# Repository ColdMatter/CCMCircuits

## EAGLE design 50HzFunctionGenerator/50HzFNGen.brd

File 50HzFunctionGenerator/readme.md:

50Hz Triangular wave generator

This circuit takes a 50Hz square wave and integrates it to turn  it into a triangular wave. 
The gain of the integrator is controlled via a trimpot and rotary switch. An external voltage offset
can also be added. This circuit is designed to drive the thorlabs cavities used in the transfer cavity
lock

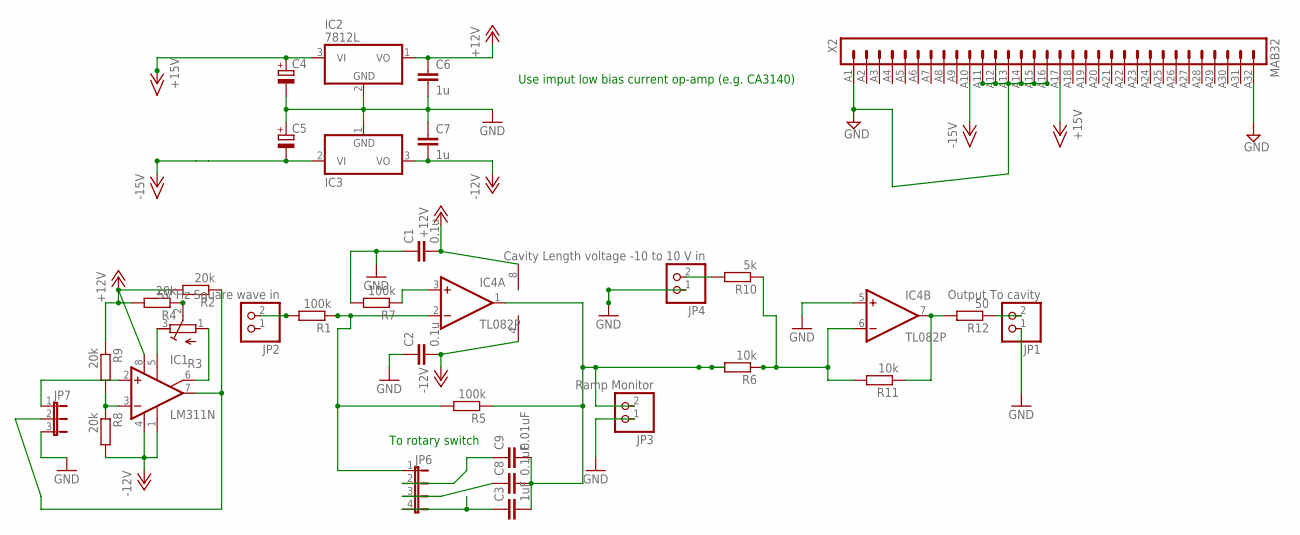
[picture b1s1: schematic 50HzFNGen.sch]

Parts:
C1, C2: 0.1u; C025-025X050
C3: 1uF; C225-062X268
C4, C5: CPOL-EUE5-8.5; E5-8,5
C6, C7: 1u; C050-030X075
C8: 0.1uF; C102-043X133
C9: 0.01uF; C050-025X075
IC1: LM311N; DIL08
IC2: 7812L; TO92
IC3: 7912L; TO92
IC4: TL082P; DIL08
JP1: Output To cavity; 1X02
JP2: 5V Hz Square wave in; 1X02
JP3: Ramp Monitor; 1X02
JP4: Cavity Length voltage -10 to 10 V in; 1X02
JP6: JP4E; JP4
JP7: JP2E; JP2
R1, R5, R7: 100k; 0207/10
R2, R4, R8, R9: 20k; 0207/10
R3: R-TRIMM64P; RTRIM64P
R6, R11: 10k; 0207/10
R10: 5k; 0207/10
R12: 50; 0207/10
X2: MAB32

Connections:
+12V: C1.2, C6.1, IC1.8 (V+), IC2.1 (VO), IC4.8 (V+), R2.2, R4.2, R9.1
+15V: C4.+, IC2.3 (VI), X2.A17 (17)
-12V: C2.2, C7.2, IC1.1 (GND), IC1.4 (V-), IC3.3 (VO), IC4.4 (V-), R8.2
-15V: C5.-, IC3.2 (VI), X2.A10 (10)
GND: C1.1, C2.1, C4.-, C5.+, C6.2, C7.1, IC2.2 (GND), IC3.1 (GND), IC4.5 (+IN), JP1.1, JP3.1, JP4.1, JP7.3, R7.2, X2.A1 (1), X2.A11 (11), X2.A12 (12), X2.A14 (14), X2.A15 (15), X2.A16 (16), X2.A32 (32)
unnamed: C3.1, JP6.4
unnamed: IC4.6 (-IN), R6.1, R10.1, R11.2
unnamed: IC4.7 (OUT), R11.1, R12.2
unnamed: JP1.2, R12.1
unnamed: C8.1, JP6.3
unnamed: IC1.7 (OUT), JP7.2, R2.1
unnamed: JP2.2, R1.2
unnamed: C3.2, C8.2, C9.2, IC4.1 (OUT), JP3.2, R5.1, R6.2
unnamed: C9.1, JP6.2
unnamed: IC1.5 (ON), R3.3 (A)
unnamed: IC4.2 (-IN), JP6.1, R1.1, R5.2
unnamed: IC1.6 (ON/STR), R3.1 (E)
unnamed: R3.2 (S), R4.1
unnamed: IC4.3 (+IN), R7.1
unnamed: JP4.2, R10.2
unnamed: IC1.2 (+IN), JP7.1
unnamed: IC1.3 (-IN), R8.1, R9.2

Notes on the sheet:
Use imput low bias current op-amp (e.g. CA3140)
To rotary switch

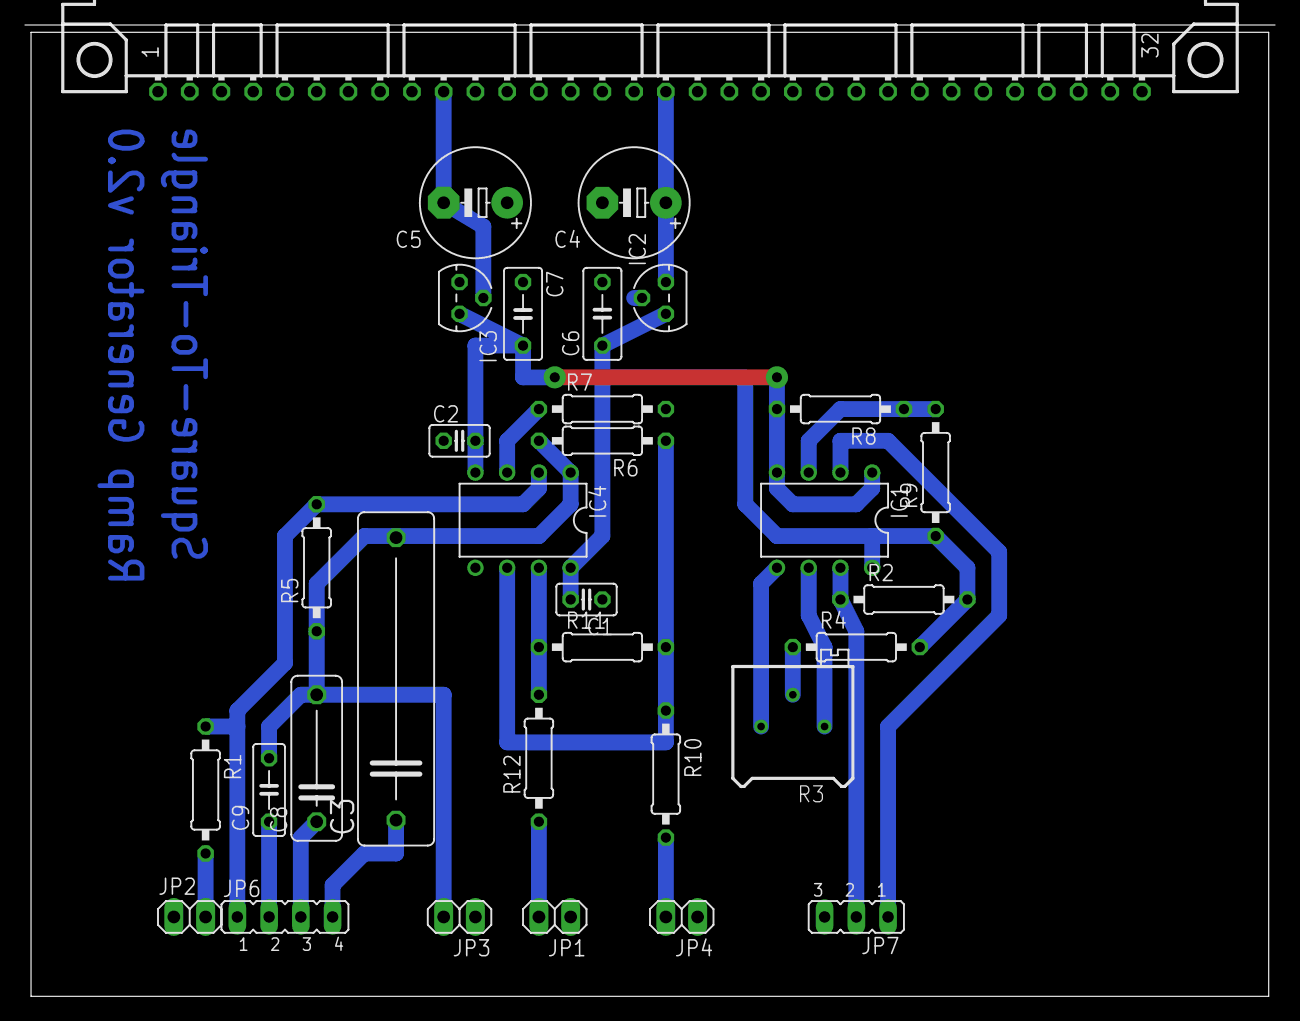
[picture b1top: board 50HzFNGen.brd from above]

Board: 2 copper layers, 100.0 x 77.7 mm, 32 parts (0 on the bottom side), 22 nets.

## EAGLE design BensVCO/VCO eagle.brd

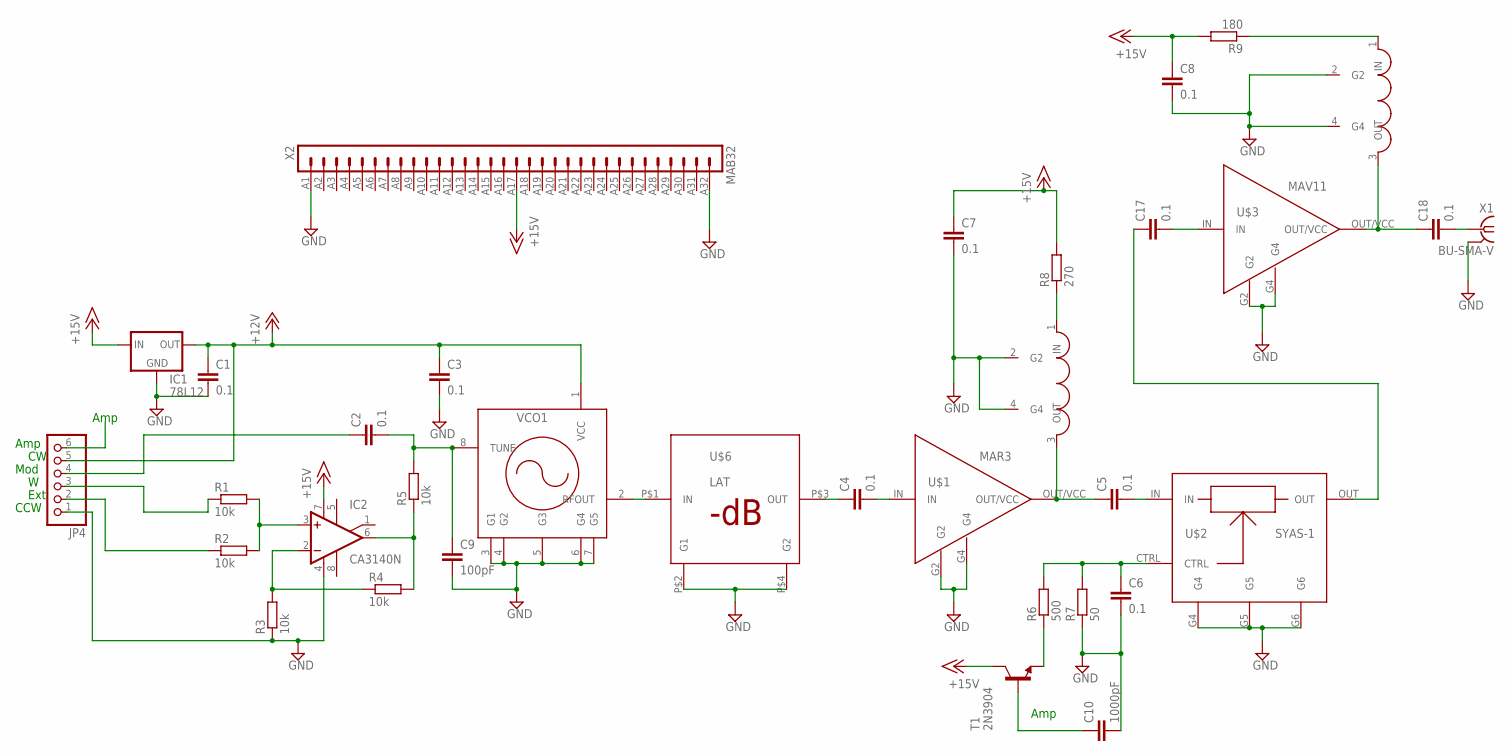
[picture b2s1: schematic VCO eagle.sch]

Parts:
C1, C2, C3, C4, C5, C6, C7, C8: 0.1; C1210
C9: 100pF; C0805
C10: 1000pF; C0805
C17, C18: 0.1; C1206
IC1: 78L12; 78LXX
IC2: CA3140N; DIL08
JP4: PINHD-1X6; 1X06
R1, R2, R3, R4, R5: 10k; 0204/7
R6: 500; 0204/7
R7: 50; 0204/7
R8: 270; R1206
R9: 180; R1206
T1: 2N3904; TO92
U$1: MAR3; MAR
U$2: SYAS-1; TTT166
U$3: MAV11; MAR
U$4, U$5: TCCH-80; PL-147
U$6: LAT; MMM168
VCO1: POS; A01
X1: BU-SMA-V
X2: MAB32

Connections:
+12V: C1.1, C3.1, IC1.OUT, JP4.5, VCO1.1 (VCC)
+15V: C7.1, C8.1, IC1.IN, IC2.7 (V+), R8.2, R9.2, T1.1 (C), X2.A17 (17)
AMP: C10.1, JP4.6, T1.2 (B)
GND: C1.2, C3.2, C6.2, C7.2, C8.2, C9.2, C10.2, IC1.GND, IC2.4 (V-), JP4.1, R3.1, R7.1, U$1.G2, U$1.G4, U$2.G4, U$2.G5, U$2.G6, U$3.G2, U$3.G4, U$4.2 (G2), U$4.4 (G4), U$5.2 (G2), U$5.4 (G4), U$6.P$2 (G1), U$6.P$4 (G2), VCO1.3 (G1), VCO1.4 (G2), VCO1.5 (G3), VCO1.6 (G4), VCO1.7 (G5), X1.2 (GND), X1.3 (GND), X1.4 (GND), X1.5 (GND), X2.A1 (1), X2.A32 (32)
unnamed: R6.1, T1.3 (E)
unnamed: JP4.2, R2.1
unnamed: IC2.3 (+IN), R1.2, R2.2
unnamed: IC2.2 (-IN), R3.2, R4.1
unnamed: IC2.6 (OUT), R4.2, R5.1
unnamed: C6.1, R6.2, R7.2, U$2.CTRL
unnamed: C2.1, JP4.4
unnamed: C2.2, C9.1, R5.2, VCO1.8 (TUNE)
unnamed: R9.1, U$5.1 (IN)
unnamed: U$6.P$1 (IN), VCO1.2 (RFOUT)
unnamed: C4.1, U$6.P$3 (OUT)
unnamed: C4.2, U$1.IN
unnamed: C5.1, U$1.OUT/VCC, U$4.3 (OUT)
unnamed: C5.2, U$2.IN
unnamed: C17.2, U$3.IN
unnamed: C18.1, U$3.OUT/VCC, U$5.3 (OUT)
unnamed: R8.1, U$4.1 (IN)
unnamed: C17.1, U$2.OUT
unnamed: C18.2, X1.1
unnamed: JP4.3, R1.1

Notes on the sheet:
CCW
Mod
Ext
Amp

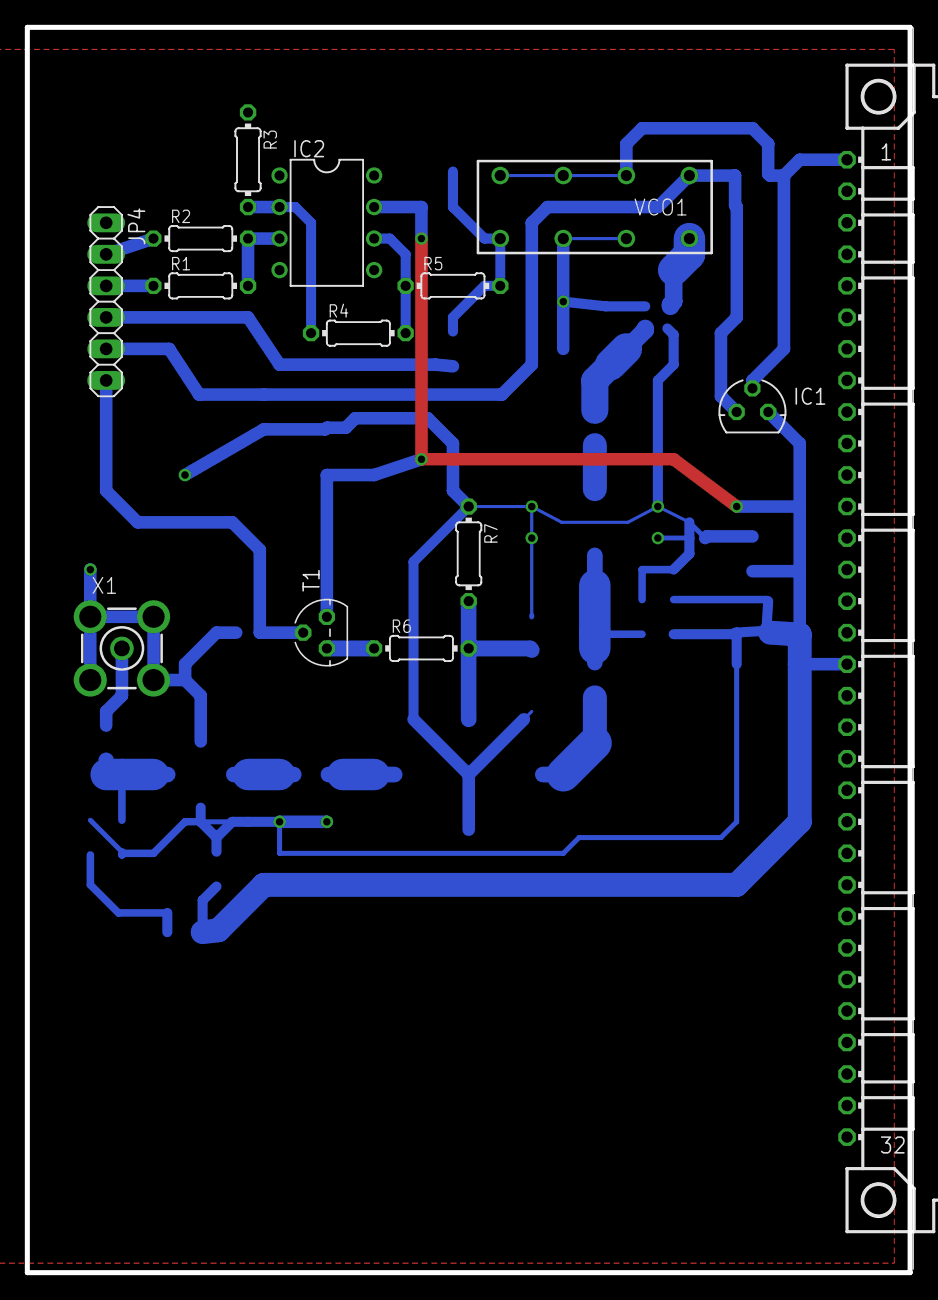
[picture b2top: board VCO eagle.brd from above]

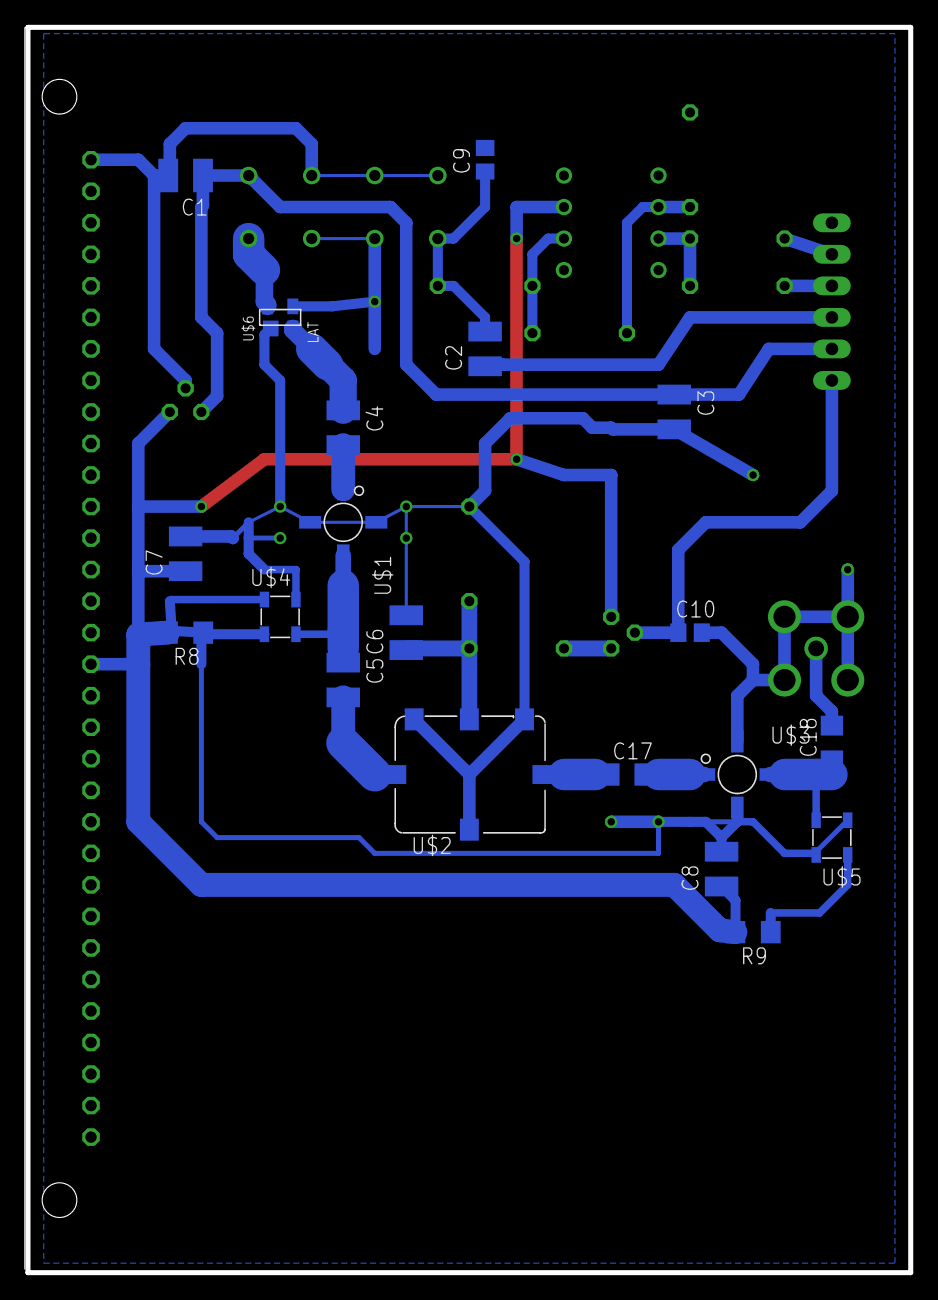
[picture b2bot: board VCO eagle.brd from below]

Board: 2 copper layers, 71.1 x 100.3 mm, 34 parts (20 on the bottom side), 24 nets.

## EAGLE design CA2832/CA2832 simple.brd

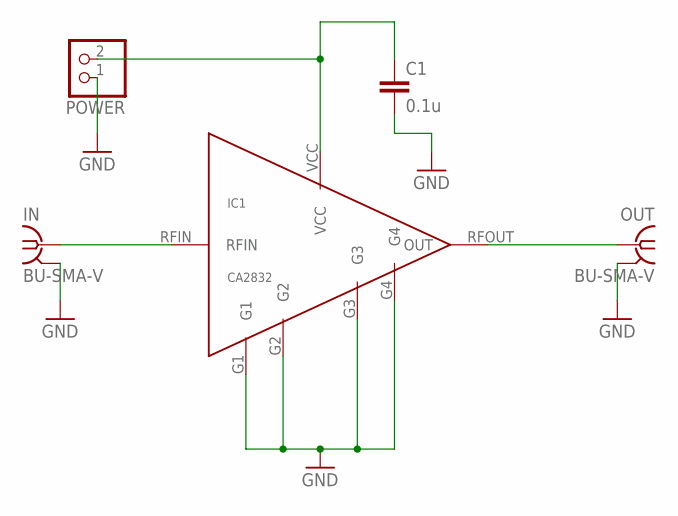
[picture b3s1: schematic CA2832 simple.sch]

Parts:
C1: 0.1u; C1206
IC1: CA2832; 714F-03
IN: BU-SMA-V
OUT: BU-SMA-V
POWER: PINHD-1X2; 1X02

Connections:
GND: C1.2, IC1.G1, IC1.G2, IC1.G3, IC1.G4, IN.2, IN.3 (2), IN.4 (2), IN.5 (2), OUT.2, OUT.3 (2), OUT.4 (2), OUT.5 (2), POWER.1
unnamed: IC1.RFIN, IN.1
unnamed: IC1.RFOUT (OUT), OUT.1
VCC: C1.1, IC1.VCC, POWER.2

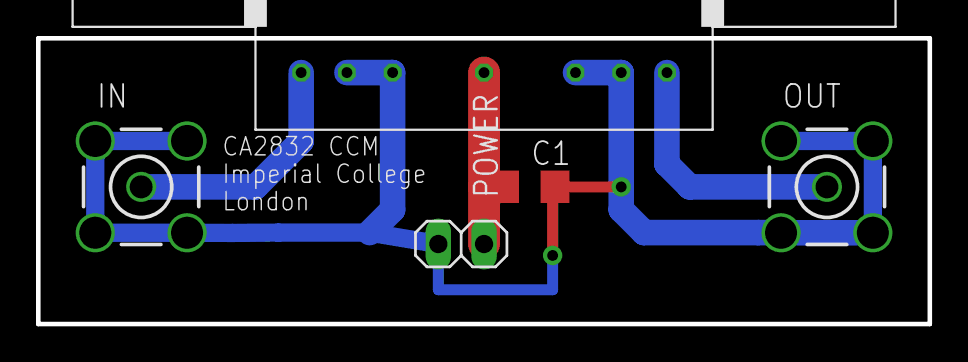
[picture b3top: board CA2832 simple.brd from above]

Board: 2 copper layers, 49.5 x 15.9 mm, 5 parts (0 on the bottom side), 4 nets.

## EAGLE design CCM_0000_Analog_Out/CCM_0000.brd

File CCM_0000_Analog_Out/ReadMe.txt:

This is a simple analog output board useful for providing an adjustable voltage to a pzt amplifier, cavity, etc.  Jumpers allow the user to choose between unipolar and bipolar operation.  Substituting various LM-4040 (or equivalent) reference diodes allows the voltage ranges to be adjusted.  

Currently, everyone in the lab uses 9V batteries with old-school trimpots wired up to them for this type of application.  Unsurprisingly, nobody ever remembers to disconnect the battery when they are finished.  As a result, we have lots of dead 9V batteries in the lab.  I've remedied the problem temporarily with some rechargeable batteries, but the practice is still stupid.

It might be a better idea to do a multi-channel board that fits nicely in a NIM rack...

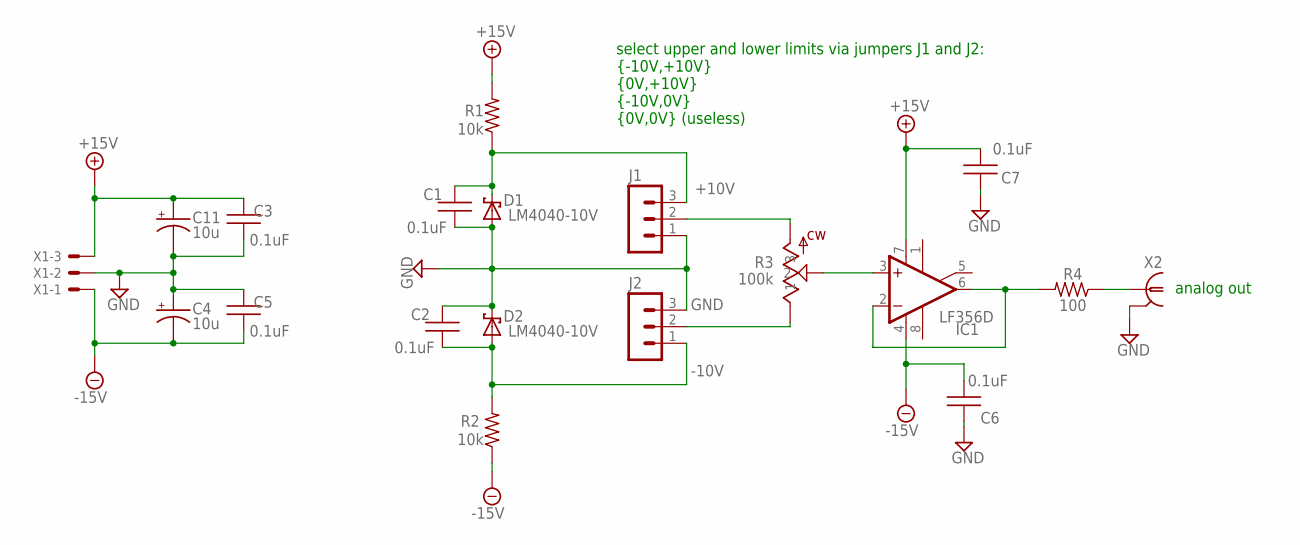
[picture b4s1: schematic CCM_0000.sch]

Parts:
C1, C2, C3, C5, C6, C7: 0.1uF; 0603
C4, C11: 10u; EIA3216
D1, D2: LM4040-10V; SOT23
IC1: LF356D; SO08
J1, J2: MA03-1
R1, R2: 10k; 0603
R3: 100k; 3590
R4: 100; 0603
X1: 22-23-2031
X2: 1-227161-0; AMP_227161

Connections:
+10V: C1.1, D1.1 (C), J1.3, R1.1
+15V: C3.1, C7.2, C11.A (+), IC1.7 (V+), R1.2, X1.3
-10V: C2.2, D2.2 (A), J2.1, R2.2
-15V: C4.C (-), C5.2, C6.2, IC1.4 (V-), R2.1, X1.1
GND: C1.2, C2.1, C3.2, C4.A (+), C5.1, C6.1, C7.1, C11.C (-), D1.2 (A), D2.1 (C), J1.1, J2.3, X1.2, X2.2
unnamed: J1.2, R3.3
unnamed: J2.2, R3.1
unnamed: R4.1, X2.1
unnamed: IC1.2 (-IN), IC1.6 (OUT), R4.2
unnamed: IC1.3 (+IN), R3.2

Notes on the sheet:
select upper and lower limits via jumpers J1 and J2: {-10V,+10V} {0V,+10V} {-10V,0V} {0V,0V} (useless)
analog out

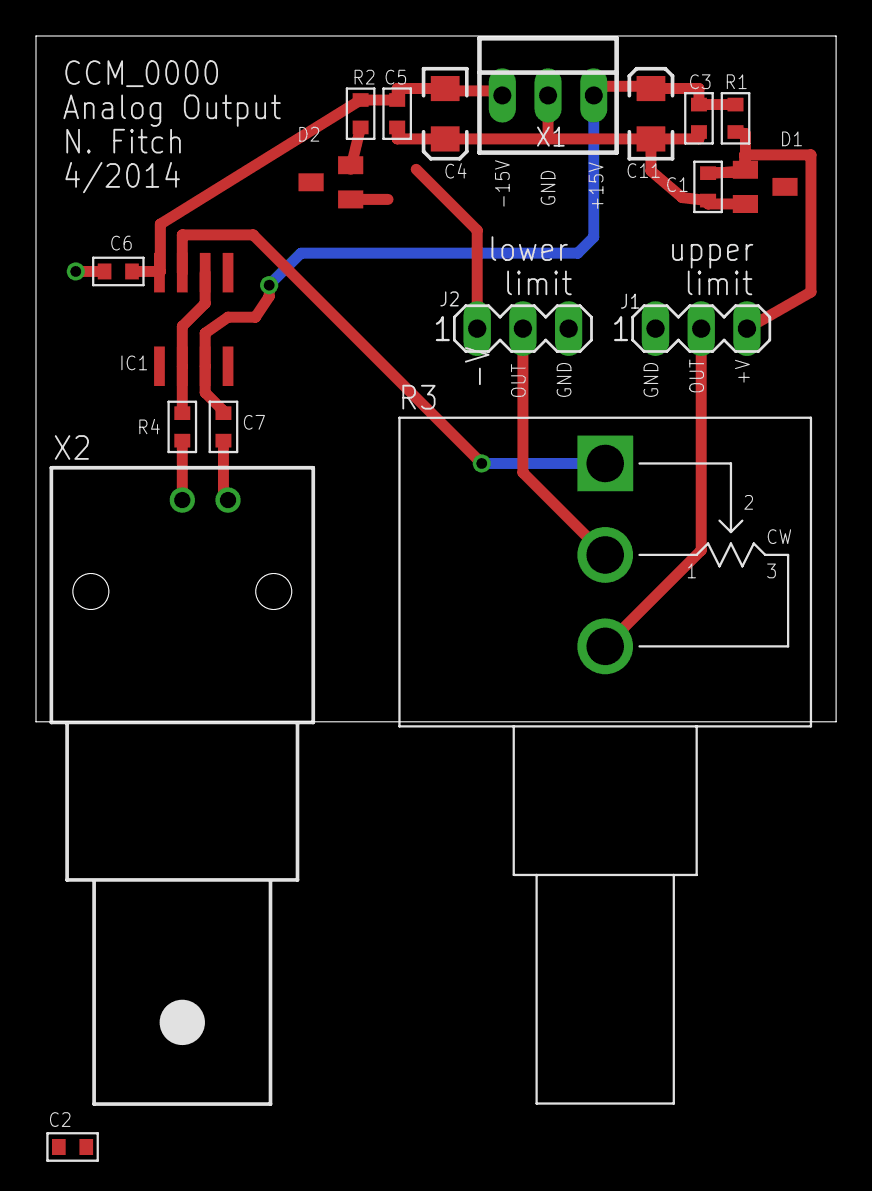
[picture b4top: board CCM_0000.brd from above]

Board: 2 copper layers, 44.5 x 38.1 mm, 19 parts (0 on the bottom side), 10 nets.

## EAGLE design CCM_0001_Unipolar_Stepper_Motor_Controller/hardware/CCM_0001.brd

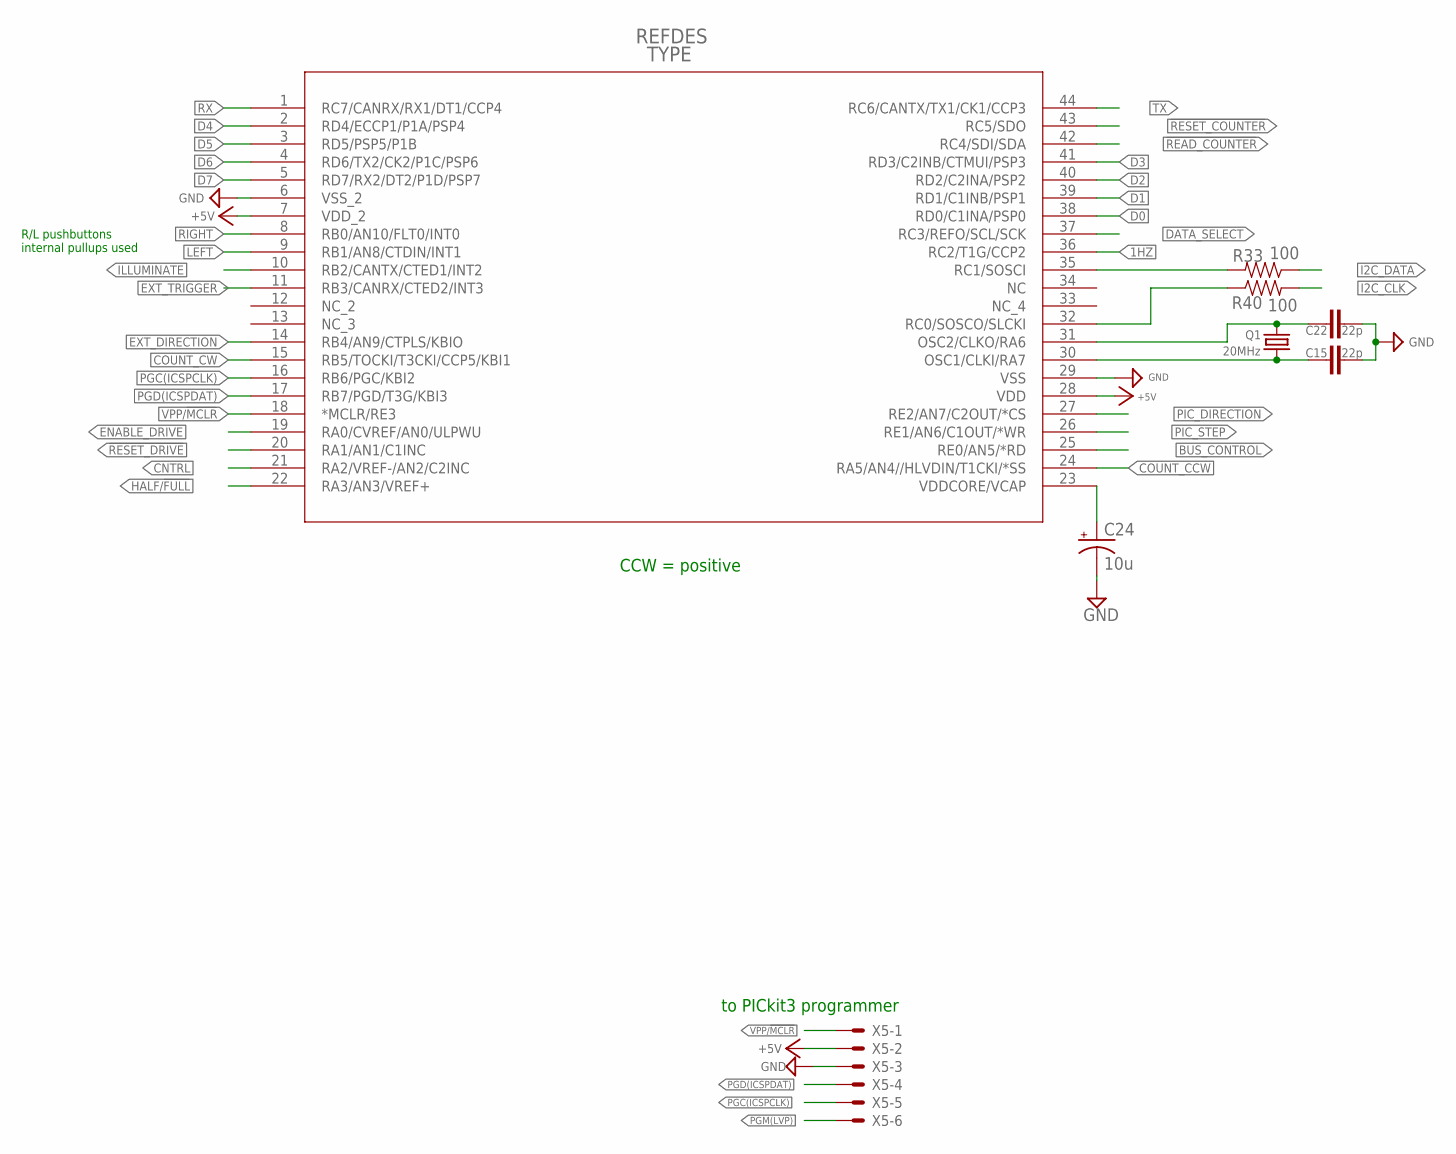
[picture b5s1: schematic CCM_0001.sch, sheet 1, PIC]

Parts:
C15, C22: 22p; 0603-CAP
C24: 10u; EIA3216
IC18: PIC18F46K80; TQFP44_MC
Q1: 20MHz; TC26V
R33, R40: 100; 0603-RES
X5: 22-23-2061

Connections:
1HZ: IC18.36 (RC2/T1G/CCP2); also elsewhere on the board
!READ_COUNTER: IC18.42 (RC4/SDI/SDA); also elsewhere on the board
!RESET_COUNTER: IC18.43 (RC5/SDO); also elsewhere on the board
!RESET_DRIVE: IC18.20 (RA1/AN1/C1INC); also elsewhere on the board
+5V: IC18.7 (VDD_2), IC18.28 (VDD), X5.2; also elsewhere on the board
BUS_CONTROL: IC18.25 (RE0/AN5/*RD); also elsewhere on the board
CNTRL: IC18.21 (RA2/VREF-/AN2/C2INC); also elsewhere on the board
COUNT_CCW: IC18.24 (RA5/AN4//HLVDIN/T1CKI/*SS); also elsewhere on the board
COUNT_CW: IC18.15 (RB5/TOCKI/T3CKI/CCP5/KBI1); also elsewhere on the board
D0: IC18.38 (RD0/C1INA/PSP0); also elsewhere on the board
D1: IC18.39 (RD1/C1INB/PSP1); also elsewhere on the board
D2: IC18.40 (RD2/C2INA/PSP2); also elsewhere on the board
D3: IC18.41 (RD3/C2INB/CTMUI/PSP3); also elsewhere on the board
D4: IC18.2 (RD4/ECCP1/P1A/PSP4); also elsewhere on the board
D5: IC18.3 (RD5/PSP5/P1B); also elsewhere on the board
D6: IC18.4 (RD6/TX2/CK2/P1C/PSP6); also elsewhere on the board
D7: IC18.5 (RD7/RX2/DT2/P1D/PSP7); also elsewhere on the board
DATA_SELECT: IC18.37 (RC3/REFO/SCL/SCK); also elsewhere on the board
ENABLE_DRIVE: IC18.19 (RA0/CVREF/AN0/ULPWU); also elsewhere on the board
EXT_DIRECTION: IC18.14 (RB4/AN9/CTPLS/KBIO); also elsewhere on the board
EXT_TRIGGER: IC18.11 (RB3/CANRX/CTED2/INT3); also elsewhere on the board
GND: C15.1, C22.1, C24.C (-), IC18.6 (VSS_2), IC18.29 (VSS), X5.3; also elsewhere on the board
HALF/!FULL: IC18.22 (RA3/AN3/VREF+); also elsewhere on the board
I2C_CLK: R40.2; also elsewhere on the board
I2C_DATA: R33.1; also elsewhere on the board
ILLUMINATE: IC18.10 (RB2/CANTX/CTED1/INT2); also elsewhere on the board
LEFT: IC18.9 (RB1/AN8/CTDIN/INT1); also elsewhere on the board
unnamed: C15.2, IC18.30 (OSC1/CLKI/RA7), Q1.1
unnamed: C22.2, IC18.31 (OSC2/CLKO/RA6), Q1.2
unnamed: C24.A (+), IC18.23 (VDDCORE/VCAP)
unnamed: IC18.35 (RC1/SOSCI), R33.2
unnamed: IC18.32 (RC0/SOSCO/SLCKI), R40.1
PGC(ICSPCLK): IC18.16 (RB6/PGC/KBI2), X5.5
PGD(ICSPDAT): IC18.17 (RB7/PGD/T3G/KBI3), X5.4
PGM(LVP): X5.6
PIC_DIRECTION: IC18.27 (RE2/AN7/C2OUT/*CS); also elsewhere on the board
PIC_STEP: IC18.26 (RE1/AN6/C1OUT/*WR); also elsewhere on the board
RIGHT: IC18.8 (RB0/AN10/FLT0/INT0); also elsewhere on the board
RX: IC18.1 (RC7/CANRX/RX1/DT1/CCP4); also elsewhere on the board
TX: IC18.44 (RC6/CANTX/TX1/CK1/CCP3); also elsewhere on the board
VPP/!MCLR: IC18.18 (*MCLR/RE3), X5.1

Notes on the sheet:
to PICkit3 programmer
R/L pushbuttons internal pullups used
CCW = positive

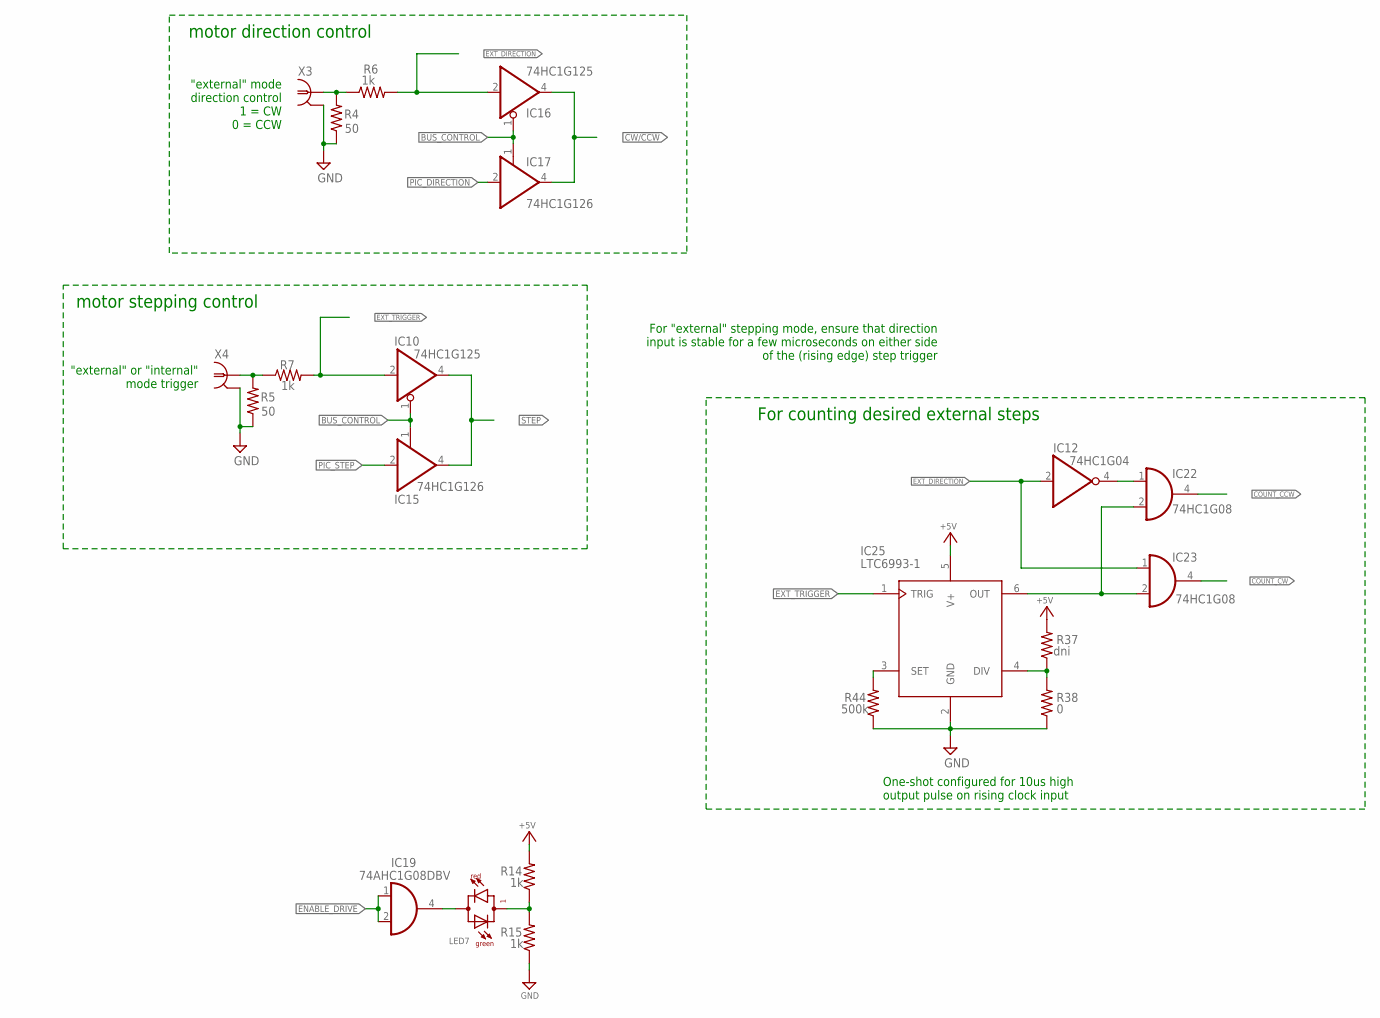
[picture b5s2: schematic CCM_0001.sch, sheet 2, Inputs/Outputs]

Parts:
IC10, IC16: 74HC1G125; SOT23-5
IC12: 74HC1G04; SOT23-5
IC15, IC17: 74HC1G126; SOT23-5
IC19: 74AHC1G08DBV; SOT23-5
IC22, IC23: 74HC1G08; SOT23-5
IC25: LTC6993-1; SOT23-6
LED7: BILED; 22-23-2021
R4, R5: 50; R2512
R6, R7, R14, R15: 1k; 0603-RES
R37: dni; 0603-RES
R38: 0; 0603-RES
R44: 500k; 0603-RES
X3, X4: 1-227161-0; AMP_227161

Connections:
+5V: IC25.5 (V+), R14.2, R37.2; also elsewhere on the board
BUS_CONTROL: IC10.1 (OE), IC15.1 (OE), IC16.1 (OE), IC17.1 (OE); also elsewhere on the board
COUNT_CCW: IC22.4 (O); also elsewhere on the board
COUNT_CW: IC23.4 (O); also elsewhere on the board
CW/!CCW: IC16.4 (O), IC17.4 (O); also elsewhere on the board
ENABLE_DRIVE: IC19.1 (I0), IC19.2 (I1); also elsewhere on the board
EXT_DIRECTION: IC12.2 (I), IC16.2 (I), IC23.1 (I0), R6.2; also elsewhere on the board
EXT_TRIGGER: IC10.2 (I), IC25.1 (TRIG), R7.2; also elsewhere on the board
GND: IC25.2 (GND), R4.1, R5.1, R15.1, R38.1, R44.1, X3.2, X4.2; also elsewhere on the board
unnamed: R5.2, R7.1, X4.1
unnamed: R4.2, R6.1, X3.1
unnamed: IC25.4 (DIV), R37.1, R38.2
unnamed: LED7.1 (CG(1)), R14.1, R15.2
unnamed: IC19.4 (O), LED7.2 (CR(2))
unnamed: IC25.3 (SET), R44.2
unnamed: IC12.4 (O), IC22.1 (I0)
unnamed: IC22.2 (I1), IC23.2 (I1), IC25.6 (OUT)
PIC_DIRECTION: IC17.2 (I); also elsewhere on the board
PIC_STEP: IC15.2 (I); also elsewhere on the board
STEP: IC10.4 (O), IC15.4 (O); also elsewhere on the board

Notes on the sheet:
One-shot configured for 10us high output pulse on rising clock input
"external" mode direction control 1 = CW 0 = CCW
"external" or "internal" mode trigger
For counting desired external steps
motor stepping control
motor direction control
For "external" stepping mode, ensure that direction input is stable for a few microseconds on either side of the (rising edge) step trigger

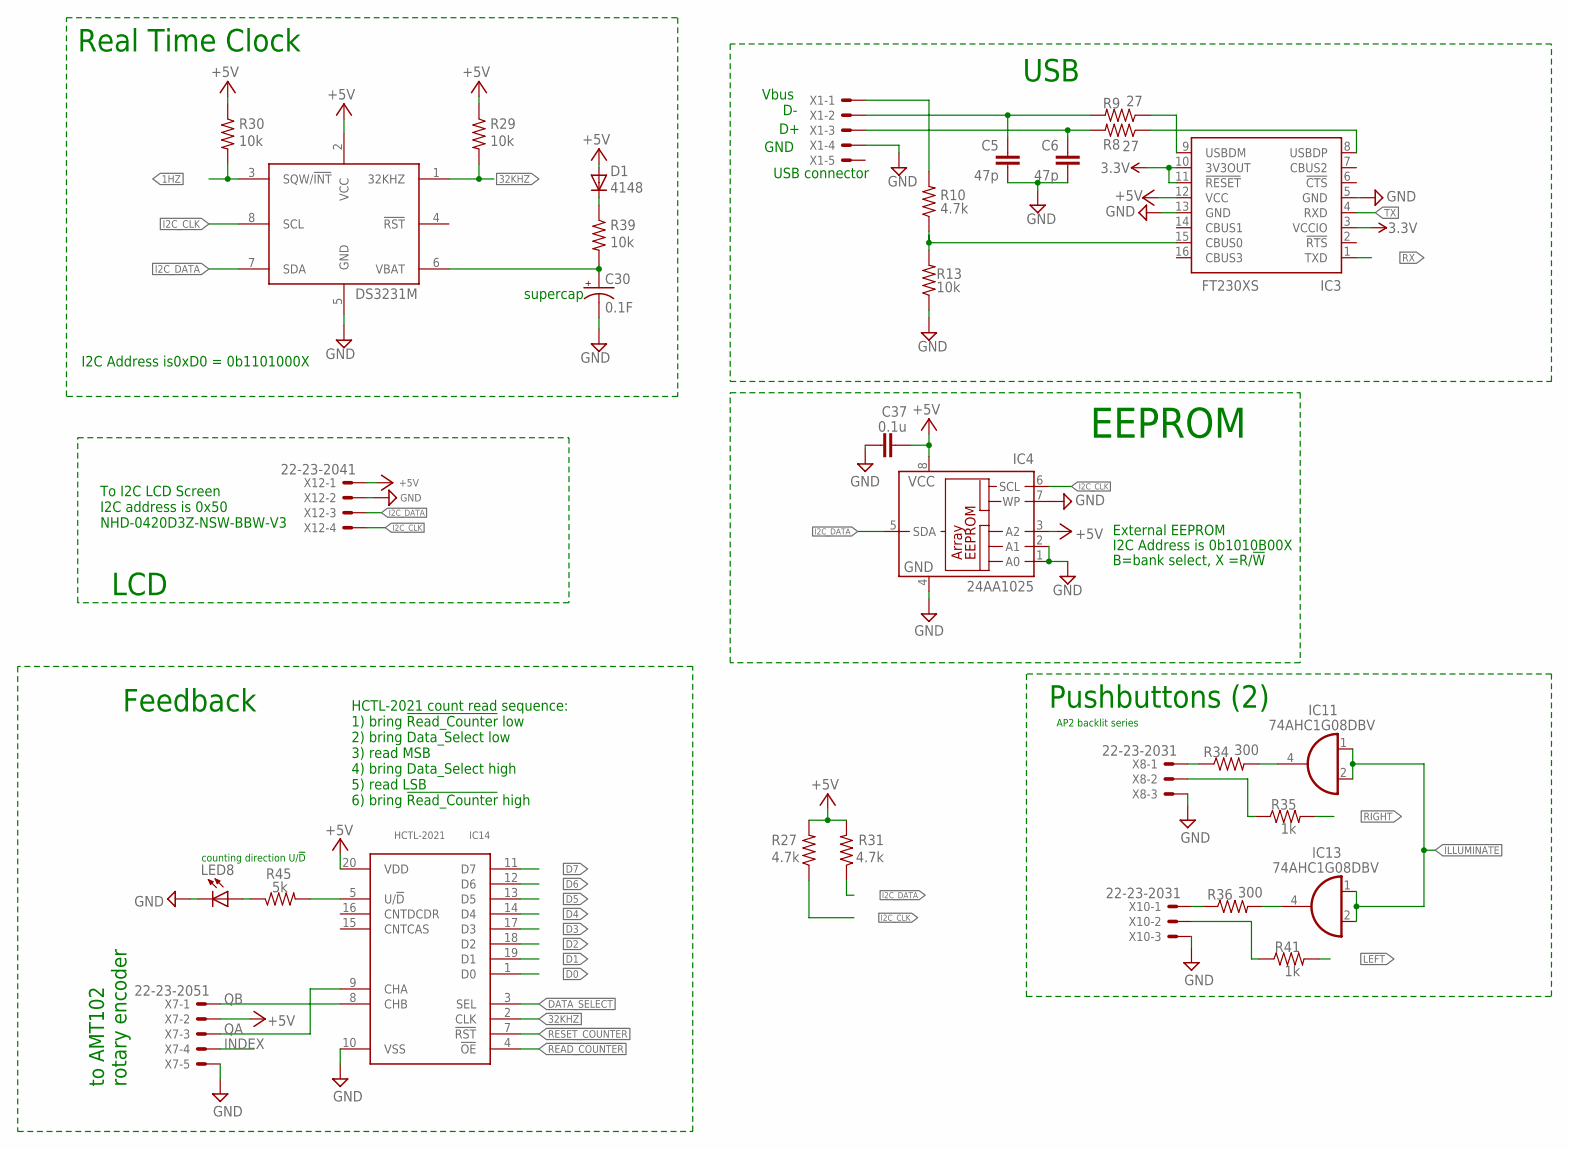
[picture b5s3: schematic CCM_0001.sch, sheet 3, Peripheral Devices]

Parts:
C5, C6: 47p; 0603-CAP
C30: 0.1F; P128-60
C37: 0.1u; 0603-CAP
D1: 4148; SOT23-3
IC3: FT230XS; SSOP16
IC4: 24AA1025; SO-08
IC6: DS3231M; 8-SOIC
IC11, IC13: 74AHC1G08DBV; SOT23-5
IC14: HCTL-2021; PLCC20
LED8: red; CHIPLED_0603
R8, R9: 27; 0603-RES
R10, R27, R31: 4.7k; 0603-RES
R13, R29, R30, R39: 10k; 0603-RES
R34, R36: 300; 0603-RES
R35, R41: 1k; 0603-RES
R45: 5k; 0603-RES
X1, X7: 22-23-2051
X8, X10: 22-23-2031
X12: 22-23-2041

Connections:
1HZ: IC6.3 (SQW/!INT), R30.2; also elsewhere on the board
3.3V: IC3.3 (VCCIO), IC3.10 (3V3OUT), IC3.11 (!RESET); also elsewhere on the board
32KHZ: IC6.1 (32KHZ), IC14.2 (CLK), R29.2
!READ_COUNTER: IC14.4 (!OE); also elsewhere on the board
!RESET_COUNTER: IC14.7 (!RST); also elsewhere on the board
+5V: C37.1, D1.1 (A), IC3.12 (VCC), IC4.3 (A2), IC4.8 (VCC), IC6.2 (VCC), IC14.20 (VDD), R27.2, R29.1, R30.1, R31.2, X7.2, X12.1; also elsewhere on the board
D0: IC14.1 (D0); also elsewhere on the board
D1: IC14.19 (D1); also elsewhere on the board
D2: IC14.18 (D2); also elsewhere on the board
D3: IC14.17 (D3); also elsewhere on the board
D4: IC14.14 (D4); also elsewhere on the board
D5: IC14.13 (D5); also elsewhere on the board
D6: IC14.12 (D6); also elsewhere on the board
D7: IC14.11 (D7); also elsewhere on the board
D+: C6.1, R8.2, X1.3
D-: C5.1, R9.2, X1.2
DATA_SELECT: IC14.3 (SEL); also elsewhere on the board
GND: C5.2, C6.2, C30.-, C37.2, IC3.5 (GND), IC3.13 (GND), IC4.1 (A0), IC4.2 (A1), IC4.4 (GND), IC4.7 (WP), IC6.5 (GND), IC14.10 (VSS), LED8.C, R13.1, X1.4, X7.5, X8.3, X10.3, X12.2; also elsewhere on the board
I2C_CLK: IC4.6 (SCL), IC6.8 (SCL), R27.1, X12.4; also elsewhere on the board
I2C_DATA: IC4.5 (SDA), IC6.7 (SDA), R31.1, X12.3; also elsewhere on the board
ILLUMINATE: IC11.1 (I0), IC11.2 (I1), IC13.1 (I0), IC13.2 (I1); also elsewhere on the board
INDEX: X7.4
LEFT: R41.2; also elsewhere on the board
unnamed: D1.3 (C), R39.1
unnamed: IC3.9 (USBDM), R9.1
unnamed: IC3.8 (USBDP), R8.1
unnamed: IC3.15 (CBUS0), R10.1, R13.2
unnamed: C30.+, IC6.6 (VBAT), R39.2
unnamed: R34.1, X8.1
unnamed: IC11.4 (O), R34.2
unnamed: R35.1, X8.2
unnamed: R36.1, X10.1
unnamed: IC13.4 (O), R36.2
unnamed: R41.1, X10.2
unnamed: LED8.A, R45.1
unnamed: IC14.5 (U/!D), R45.2
QA: IC14.9 (CHA), X7.3
QB: IC14.8 (CHB), X7.1
RIGHT: R35.2; also elsewhere on the board
RX: IC3.1 (TXD); also elsewhere on the board
TX: IC3.4 (RXD); also elsewhere on the board
VBUS: R10.2, X1.1

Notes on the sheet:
USB connector
I2C Address is0xD0 = 0b1101000X
supercap
Real Time Clock
USB
To I2C LCD Screen I2C address is 0x50 NHD-0420D3Z-NSW-BBW-V3
to AMT102 rotary encoder
HCTL-2021 count read sequence: 1) bring !Read_Counter! low 2) bring Data_Select low 3) read MSB 4) bring Data_Select high 5) read LSB 6) bring !Read_Counter! high
counting direction U/!D!
Feedback
Pushbuttons (2)
AP2 backlit series
Vbus
GND
LCD
I2C Address is 0b1010B00X
B=bank select, X =R/!W
External EEPROM
EEPROM
